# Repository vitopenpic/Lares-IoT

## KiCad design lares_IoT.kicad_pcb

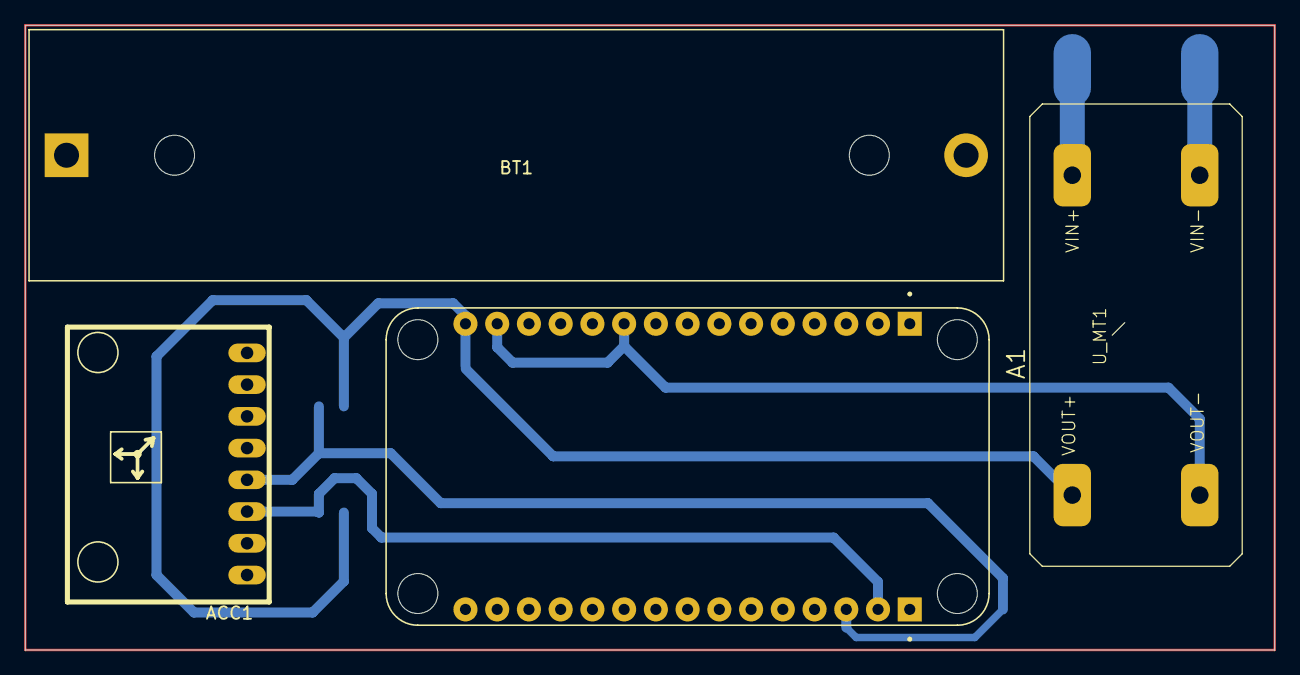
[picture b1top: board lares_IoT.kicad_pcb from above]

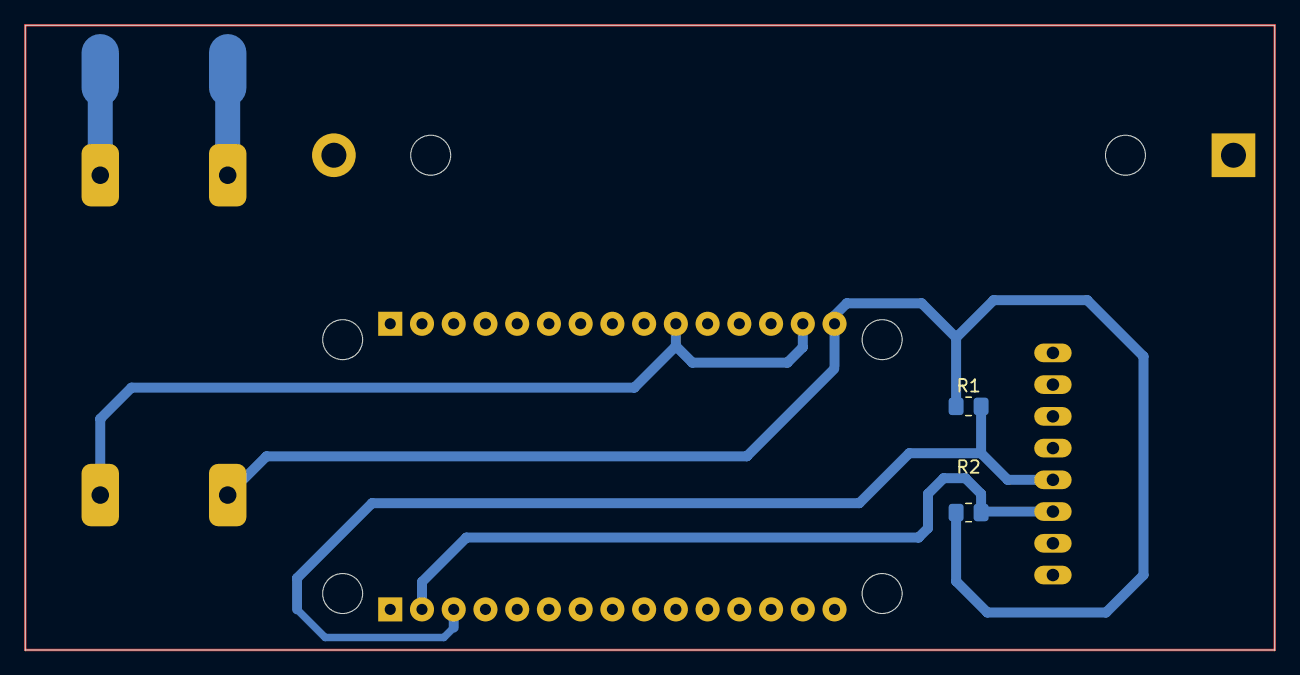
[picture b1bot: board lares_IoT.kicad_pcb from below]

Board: 2 copper layers, 100.0 x 50.0 mm, 6 parts (2 on the bottom side), 6 nets.

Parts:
A1: esp8266; SEEED_113990105
ACC1: GY-521
BT1: Battery_Cell; BatteryHolder_MPD_BH-18650-PC2
R1, R2: R; R_0805
U_MT1: MT3608_board

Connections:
/Vcc: A1.J1_15 (VIN), R1.1, R2.1, U_MT1.3 (VOUT+)
unnamed: A1.J2_2 (D1), ACC1.SCL, R2.2
unnamed: A1.J2_3 (D2), ACC1.SDA, R1.2
unnamed: BT1.1 (+), U_MT1.1 (VIN+)
unnamed: BT1.2 (-), U_MT1.2 (VIN-)
unnamed: A1.J1_10 (GND), A1.J1_14 (GND), U_MT1.4 (VOUT-)
